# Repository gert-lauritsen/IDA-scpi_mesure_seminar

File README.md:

## Formål:

Dette seminar har til formål at introducere og demonstrere anvendelsen af forskellige måleinstrumenter i kombination med SCPI-styring via Python. Deltagerne vil få hands-on erfaring med oscilloskop, elektronisk belastning, multimeter og funktionsgenerator, samt test og analyse af USB-signaler, frekvens-sweep, low-noise og high-speed målinger.

# Indhold:

* Introduktion til Måleteknik og SCPI
* Grundlæggende teori om præcisionsmåling og signalanalyse
* Introduktion til SCPI (Standard Commands for Programmable Instruments)
* Fordele ved automatiseret måling med Python

Opsætning af Testmiljø

* Forbindelse af oscilloskop, elektronisk belastning, multimeter og funktionsgenerator
* Kommunikation mellem instrumenter og PC via SCPI

Praktiske eksempler på opsætning og fejlfinding

* Måling og Analyse af USB Signaler
* Måling af spænding, strøm og signalintegritet

Brug af oscilloskop til at analysere USB-dataoverførsel

* Identifikation af signalstøj og forstyrrelser
* Frekvens Sweep og Signalrespons
* Generering af frekvens-sweep med funktionsgenerator
* Måling af respons ved forskellige frekvenser
* Analyse af resonans og filterkarakteristik
* Low-Noise og High-Speed Målinger
* Teknikker til reduktion af støj i målinger
* Brug af differentielle målinger og skærmning
* Håndtering af højhastighedssignaler og signalintegritet

# Praktiske Øvelser og Hands-on Test

* Implementering af automatiserede tests med Python og SCPI
* Målinger med fokus på signalanalyse
  Diskussion og erfaringsudveksling

# Målgruppe:

Ingeniører, teknikere og studerende med interesse for elektronik og præcisionsmåling.
Krav til deltagere:  
Grundlæggende kendskab til elektronik og måleteknik
Erfaring med Python-programmering er en fordel, men ikke et krav
Forventet udbytte:

Deltagerne vil efter seminaret have praktisk erfaring med opsætning og anvendelse af måleinstrumenter i kombination med SCPI-styring. De vil kunne foretage automatiserede målinger og analyse af elektriske signaler på en systematisk og præcis måde.

Note

Problmer med NI

1\) Restart NI services

* Close NI MAX and any NI apps.
* Press Win + R → type services.msc.
* Restart these (if present):
* NI Configuration Manager
* NI Device Loader
* NI mDNS Responder Service
* NI PXI Resource Manager

NI max lister aktive instruments

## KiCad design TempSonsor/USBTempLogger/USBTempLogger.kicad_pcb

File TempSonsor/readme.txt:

Taget udgangspunkt i:
https://github.com/Jana-Marie/stm32g4xx_usb_cdc/tree/main

Andre scpi interface
Arduino:
https://github.com/Vrekrer/Vrekrer_scpi_parser

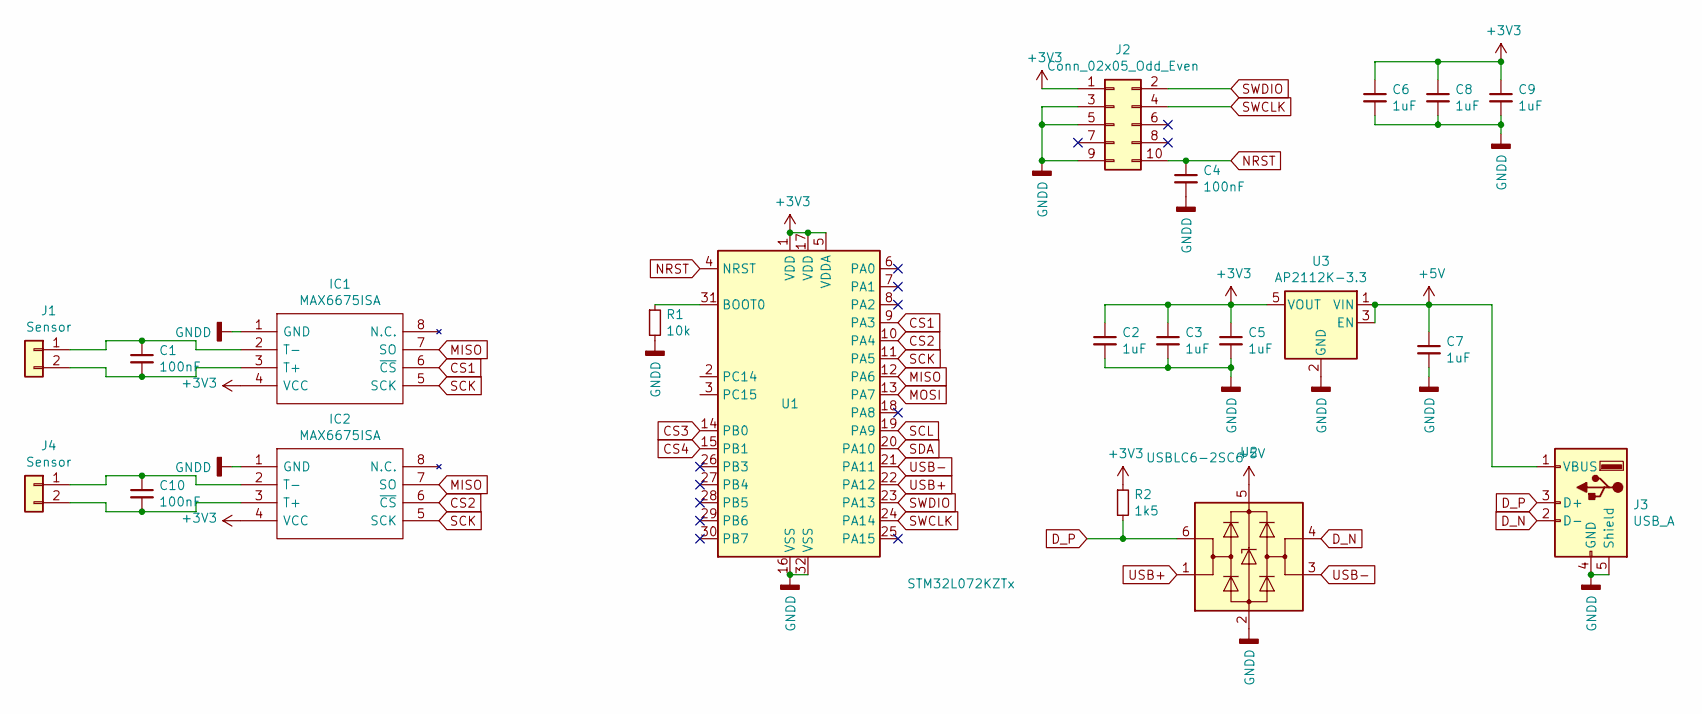
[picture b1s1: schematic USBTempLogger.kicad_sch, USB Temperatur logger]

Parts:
C1, C4, C10: 100nF; C_0805_2012Metric
C2, C3, C5, C6, C7, C8, C9: 1uF; C_0805_2012Metric
IC1, IC2: MAX6675ISA; SOIC127P600X175-8N; Mouser Part Number N/A
J1, J4: Sensor; Molex_KK-254_AE-6410-02A_1x02_P2.54mm_Vertical
J2: Conn_02x05_Odd_Even; PinHeader_2x05_P1.27mm_Vertical_SMD
J3: USB_A; USB_Mini-B_Wuerth_65100516121_Horizontal
R1: 10k; R_0805_2012Metric
R2: 1k5; R_0805_2012Metric
U1: STM32L072KZTx; LQFP-32_7x7mm_P0.8mm
U2: USBLC6-2SC6; SOT-23-6
U3: AP2112K-3.3; SOT-23-5

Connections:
+3V3: C2.1, C3.1, C5.1, C6.1, C8.1, C9.1, IC1.4 (VCC), IC2.4 (VCC), J2.1, R2.1, U1.1 (VDD), U1.5 (VDDA), U1.17 (VDD), U3.5 (VOUT)
+5V: C7.1, J3.1 (VBUS), U2.5 (VBUS), U3.1 (VIN), U3.3 (EN)
CS1: IC1.6 (~CS), U1.9 (PA3)
CS2: IC2.6 (~CS), U1.10 (PA4)
CS3: U1.14 (PB0)
CS4: U1.15 (PB1)
D_N: J3.2 (D-), U2.4 (I/O2)
D_P: J3.3 (D+), R2.2, U2.6 (I/O1)
GNDD: C2.2, C3.2, C4.2, C5.2, C6.2, C7.2, C8.2, C9.2, IC1.1 (GND), IC2.1 (GND), J2.3, J2.5, J2.9, J3.4 (GND), J3.5 (Shield), R1.2, U1.16 (VSS), U1.32 (VSS), U2.2 (GND), U3.2 (GND)
MISO: IC1.7 (SO), IC2.7 (SO), U1.12 (PA6)
MOSI: U1.13 (PA7)
NRST: C4.1, J2.10, U1.4 (NRST)
unnamed: C1.2, IC1.3 (T+), J1.2
unnamed: C1.1, IC1.2 (T-), J1.1
unnamed: C10.2, IC2.3 (T+), J4.2
unnamed: C10.1, IC2.2 (T-), J4.1
unnamed: R1.1, U1.31 (BOOT0)
SCK: IC1.5 (SCK), IC2.5 (SCK), U1.11 (PA5)
SCL: U1.19 (PA9)
SDA: U1.20 (PA10)
SWCLK: J2.4, U1.24 (PA14)
SWDIO: J2.2, U1.23 (PA13)
USB+: U1.22 (PA12), U2.1 (I/O1)
USB-: U1.21 (PA11), U2.3 (I/O2)

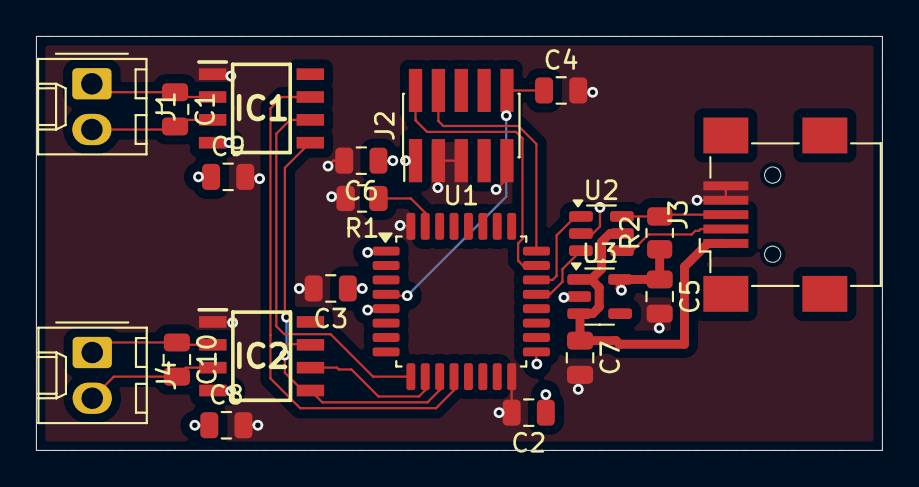
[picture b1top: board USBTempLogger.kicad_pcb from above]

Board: 4 copper layers, 47.0 x 23.0 mm, 21 parts (0 on the bottom side), 19 nets.

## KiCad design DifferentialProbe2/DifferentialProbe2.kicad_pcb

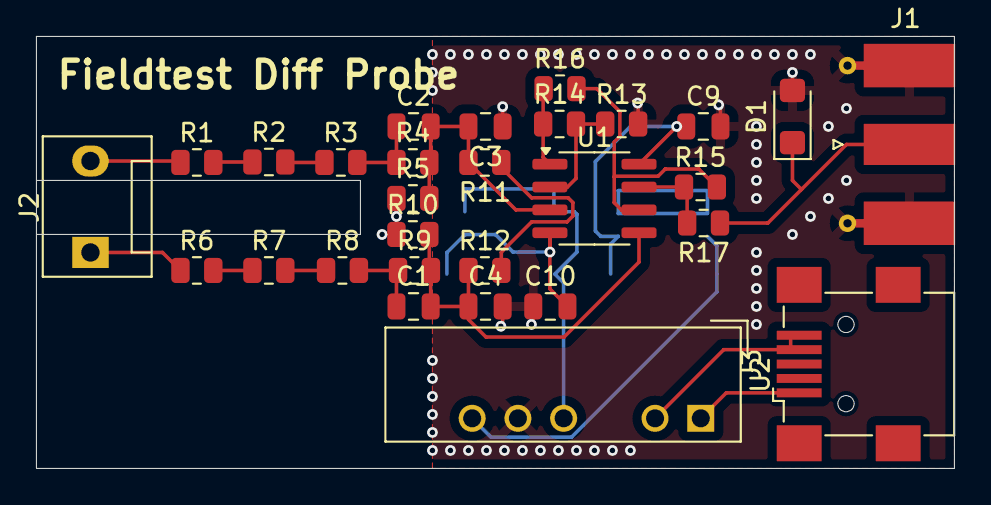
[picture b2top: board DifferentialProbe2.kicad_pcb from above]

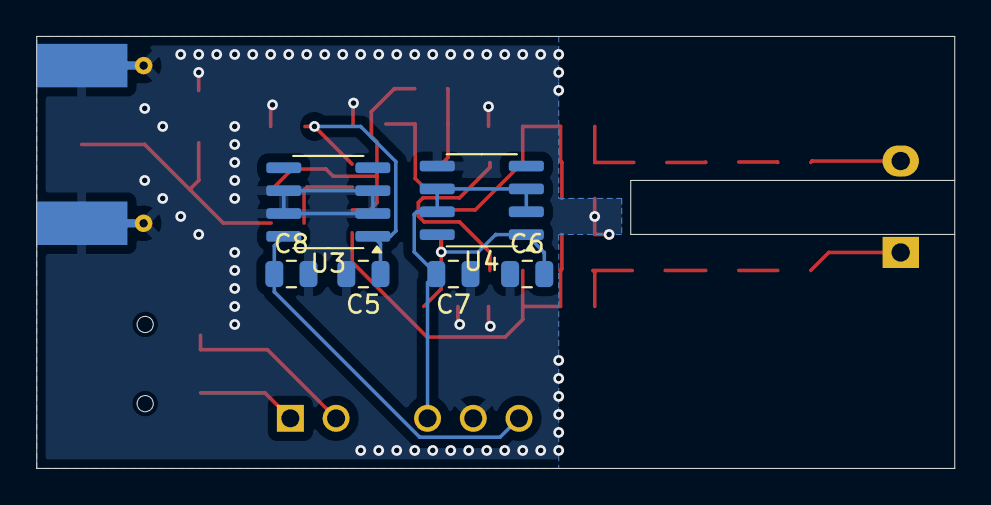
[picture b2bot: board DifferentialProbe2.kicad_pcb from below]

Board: 2 copper layers, 51.0 x 24.0 mm, 35 parts (6 on the bottom side), 23 nets.

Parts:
C1, C2, C3, C4: 33p; C_0805_2012Metric
C5, C6, C7, C8, C9, C10: 100nF; C_0805_2012Metric
D1: SMF24A; D_SMF
J1: Conn_Coaxial; SMA_Molex_73251-1153_EdgeMount_Horizontal
J2: Conn_01x03; FanPinHeader_1x03_P2.54mm_Vertical
J3: USB_A; USB_Mini-B_Wuerth_65100516121_Horizontal
R1, R2, R3, R4, R6, R7, R8, R9: 270K; R_0805_2012Metric
R5, R10, R11, R12: 10k9; R_0805_2012Metric
R13, R14, R15, R16: 10k; R_0805_2012Metric
R17: 50R; R_0805_2012Metric
U1: LM4562; SOIC-8_3.9x4.9mm_P1.27mm
U2: TMA-1215D; Converter_DCDC_TRACO_TMA-05xxD_12xxD_Dual_THT
U3: MC78L05_SO8; SOIC-8_3.9x4.9mm_P1.27mm
U4: MC79L12_SO8; SOIC-8_3.9x4.9mm_P1.27mm

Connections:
GND: C3.1, C4.2, C5.2, C6.1, C7.1, C8.2, C9.2, C10.1, D1.2 (A2), J1.2 (Ext), R5.1, R10.1, R13.2, U2.5 (Com), U3.2 (GND), U3.3 (GND), U3.6 (GND), U3.7 (GND), U4.5 (GND)
GNDD: J3.4 (GND), J3.5 (Shield), U2.2 (-Vin)
unnamed: C1.1, R8.2, R9.1
unnamed: C2.1, R3.2, R4.1
unnamed: D1.1 (A1), J1.1 (In), R17.1
unnamed: J2.1, R6.1
unnamed: J2.3, R1.1
unnamed: J3.1 (VBUS), U2.1 (+Vin)
unnamed: R1.2, R2.1
unnamed: R2.2, R3.1
unnamed: R6.2, R7.1
unnamed: R7.2, R8.1
unnamed: R11.1, R12.2
unnamed: R14.1, R16.1, U1.1
unnamed: R15.1, R17.2, U1.7
unnamed: C2.2, C3.2, R4.2, R5.2, R11.2, U1.3 (+)
unnamed: R13.1, R14.2, U1.2 (-)
unnamed: C1.2, C4.1, R9.2, R10.2, R12.1, U1.5 (+)
unnamed: R15.2, R16.2, U1.6 (-)
unnamed: C5.1, C9.1, U1.8 (V+), U3.1 (OUT)
unnamed: C6.2, C10.2, U1.4 (V-), U4.1 (OUT)
unnamed: C8.1, U2.6 (+Vout), U3.8 (IN)
unnamed: C7.2, U2.4 (-Vout), U4.2 (IN), U4.3 (IN), U4.6 (IN), U4.7 (IN)

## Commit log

2025-09-20 init
